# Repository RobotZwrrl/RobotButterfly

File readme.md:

# Robot Butterfly

[Robot Butterfly](http://robotzwrrl.xyz/robot-butterfly/) invites you to experience nature's elegance alongside it, while interacting with the surrounding wilderness! [Available now as a kit](https://robotmissions.org/store/) to build yourself. 

For more information, check out: [robotzwrrl.xyz/robot-butterfly](http://robotzwrrl.xyz/robot-butterfly/). As well, see the [instructions](https://robotzwrrl.xyz/robot-butterfly/instructions/chapter01.php) to build your own!

Robot Butterfly's design files are released as open source hardware, provided under these unique terms: If you replicate it, please take a photo of it in nature and email it to me with the city and its nickname! ☺️

---

## Bug Fix 12-15-24

A 3D printable bugfix is available! The three pieces to print are:

- [Servo Horn Indent L](https://github.com/RobotGrrl/RobotButterfly/blob/main/3dprint/servo_horn_indent_L_v1.0.stl)
- [Servo Horn Indent R](https://github.com/RobotGrrl/RobotButterfly/blob/main/3dprint/servo_horn_indent_R_v1.0.stl)
- [Spacer Back](https://github.com/RobotGrrl/RobotButterfly/blob/main/3dprint/spacer_back_v1.1.stl)

The servo horn piece has been updated to work with the new horns that have an indent, rather than being flat in the previous version. The horn is placed on the side that has the arrow indicator. The fasteners go through holes #1 and #4. See photo below for reference.

The spacer back piece has been updated to have clearance for the chamfer around the switch housing on the enclosure. This provides a cleaner fit and smoother lid installation process.

---

## Electronics

The Butterfly Chonky board connects with [Keystone](https://github.com/RobotGrrl/Keystone) and [Boostlet!](https://github.com/RobotGrrl/boostlet). Those two boards are also open source, and can be found in these repositories:

- https://github.com/RobotGrrl/boostlet
- https://github.com/RobotGrrl/Keystone

### What do the LEDs mean?

There are a few LEDs that are visible through the windows on the back of the enclosure.

On Chonky, there are two yellow 5 mm LEDs. On the left hand side, is D2. In the firmware, D2 is `LED_COMMS_PIN` (pin 5). On the right hand side, this is D1. In the firmware, D1 is `LED_HEARTBEAT_PIN` (pin 13).

LEDs from Keystone are also visible through the LED ports on the back side of the enclosure. As well, sometimes their brightness reflects in Chonky’s 5 mm LEDs. On the left hand side is power. The power LED is on all the time. On the right hand side are TX and RX. The TX and RX LEDs are activated whenever there is data on the serial port. This can be useful for a visual check, but it also just looks techno cool.

In the inaugural version, all the LEDs are yellow, which can sometimes make it tricky to visually differentiate between Chonky and Keystone's LEDs. This will be changed in a future production revision :)

---

## Manufacturing

| Piece                     | Layer height    | Supports                   | Infill | Shells | Notes                                              |
| ------------------------- | --------------- | -------------------------- | ------ | ------ | -------------------------------------------------- |
| enclosure_v1.0.stl        | 0.25 mm DRAFT   | Everwhere, Organic         | 15%    | 2      | \-                                                 |
| neopixel_bracket_v1.0.stl | 0.25 mm DRAFT   | Everwhere, Organic         | 15%    | 3      | Prints standing up                                 |
| battery_bracket_v1.0.stl  | 0.25 mm DRAFT   | Supports to build platform | 15%    | 2      | Hiya!' faces up, Top fill pattern: Octogram Spiral |
| lid_v1.1.stl              | 0.25 mm DRAFT   | None                       | 15%    | 3      | Chamfer side down                                                 |
| servo_bracket_v1.0.stl    | 0.25 mm DRAFT   | None                       | 15%    | 2      | Prints face down                                   |
| servo_horn_indent_L_v1.0.stl     | 0.20 mm QUALITY | None                       | 20%    | 4      | \-                                                 |
| servo_horn_indent_R_v1.0.stl     | 0.20 mm QUALITY | None                       | 20%    | 4      | \-                                                 |
| cover_v1.0.stl            | 0.25 mm DRAFT   | None                       | 15%    | 2      | Cool!' faces up                                    |
| spacer_back_v1.1.stl      | 0.25 mm DRAFT   | None                       | 15%    | 2      | Chamfer side down                                  |
| spacer_front_v1.0.stl     | 0.25 mm DRAFT   | None                       | 15%    | 2      | Chamfer side down                                  |
| wing_L_v1.0.stl           | 0.25 mm DRAFT   | None                       | 15%    | 3      | Top & bottom fill pattern: Archimedian Chords. Print 1st layer at a very slow speed.      |
| wing_R_v1.0.stl           | 0.25 mm DRAFT   | None                       | 15%    | 3      | Top & bottom fill pattern: Archimedian Chords. Print 1st layer at a very slow speed.      |

---

## Firmware

**Firmware is in active development**

Download the [Robot Butterfly library](https://github.com/RobotZwrrl/RobotButterfly/tree/main/firmware/library/RobotButterfly) and install it into your Arduino library folder _(for example: ~/Documents/Arduino/libraries)_.

### Boards Manager

In the Arduino IDE boards manager (Tools > Board > Board Manager), search for **esp32**. Under **esp32 by Espressif Systems**, choose **2.0.4**, and install it.

### Library Dependencies

In the Arduino IDE library manager (Tools > Manage Libraries), please install the following libraries with the designated versions:

- [Streaming](https://github.com/janelia-arduino/Streaming) - v5.0.0
- [movingAvg](https://github.com/JChristensen/movingAvg) - v2.3.2
- [MPU6050](https://github.com/ElectronicCats/mpu6050) - v1.4.3
- [Adafruit Neopixel](https://github.com/adafruit/Adafruit_NeoPixel) - v.1.12.4
- [ESP32Servo](https://github.com/madhephaestus/ESP32Servo) - v3.0.6 
- [ServoEasing](https://github.com/ArminJo/ServoEasing) - v3.4.0
- [DHT](https://github.com/adafruit/DHT-sensor-library) - v1.4.6
- [Adafruit Unified Sensor](https://github.com/adafruit/Adafruit_Sensor) - v1.1.15 
- [HC-SR04](https://github.com/d03n3rfr1tz3/HC-SR04) - v1.1.3 

### Upload Code

Here's how to upload code to Robot Butterfly!

_Please see steps above to ensure all dependencies are installed properly_

1. Tools > Board > esp32 > Set board to **ESP32 Dev Module**

2. Tools > Set upload speed to **115200 baud** (at the bottom of the menu)

3. Tools > Set CPU speed to **80 MHz** (first setting after a divider in the menu)

4. Tools > Manage Libraries
There are library dependencies that will need to be downloaded, see list above

5. Open a Robot Butterfly example sketch

6. Plug in Robot Butterfly

7. Tools > Port > Select the port

8. Upload

9. Congrats! You have uploaded code to Robot Butterfly!

### Animations

For developers - here's how to make your own animation (servo and neopixel):

1. Add identifier to enum servoAnimName

`SERVO_ANIM_SOARING`

2. Add the run function prototype

`void runServoAnim_soaring(struct ServoAnimation *animation);`

3. Write the run function

`void runServoAnim_soaring(struct ServoAnimation *a) { ... }`

4. Write the init function

`void initServoAnim_soaring(struct ServoAnimation *a) { ... }`

5. Add the case to setServoAnim

`case SERVO_ANIM_SOARING: 
initServoAnim_soaring(a); 
break;`

6. Call the animation to run it!

`setServoAnim(&servo_animation_alert, SERVO_ANIM_SOARING, SERVO_ANIM_ALERT); 
startServoAnim(&servo_animation_alert);`

---

## Debugging

Please see [this page for debugging FAQ](https://robotzwrrl.xyz/robot-butterfly/instructions/debugging.php).

---

## License

Robot Butterfly (C) Copyright Erin RobotZwrrl, Robot Missions Inc.

05-30-24 v1.0

[RobotZwrrl.xyz/robot-butterfly](http://RobotZwrrl.xyz/robot-butterfly)

[RobotMissions.org](https://RobotMissions.org)

This hardware is released under:

CERN Open Hardware License Version 2.0 - Permissive (CERN-OHL-P)

[https://cern-ohl.web.cern.ch/](https://cern-ohl.web.cern.ch/)

The software is released under:

The MIT License

[https://opensource.org/license/mit](https://opensource.org/license/mit)

The documentation is released under:

CC-BY-SA-4.0

[https://creativecommons.org/licenses/by-sa/4.0/](https://creativecommons.org/licenses/by-sa/4.0/)

_Disclaimer: Distributed as is. No warranty is given. Not responsible or liable for any damage or harm that result from this product._

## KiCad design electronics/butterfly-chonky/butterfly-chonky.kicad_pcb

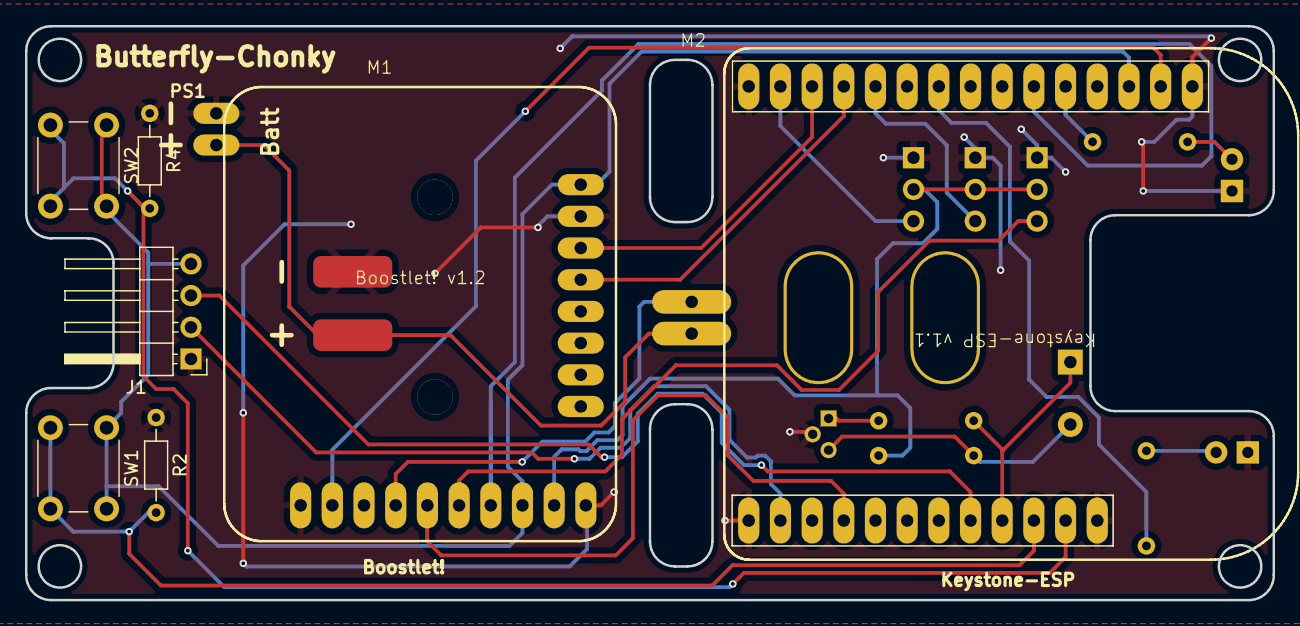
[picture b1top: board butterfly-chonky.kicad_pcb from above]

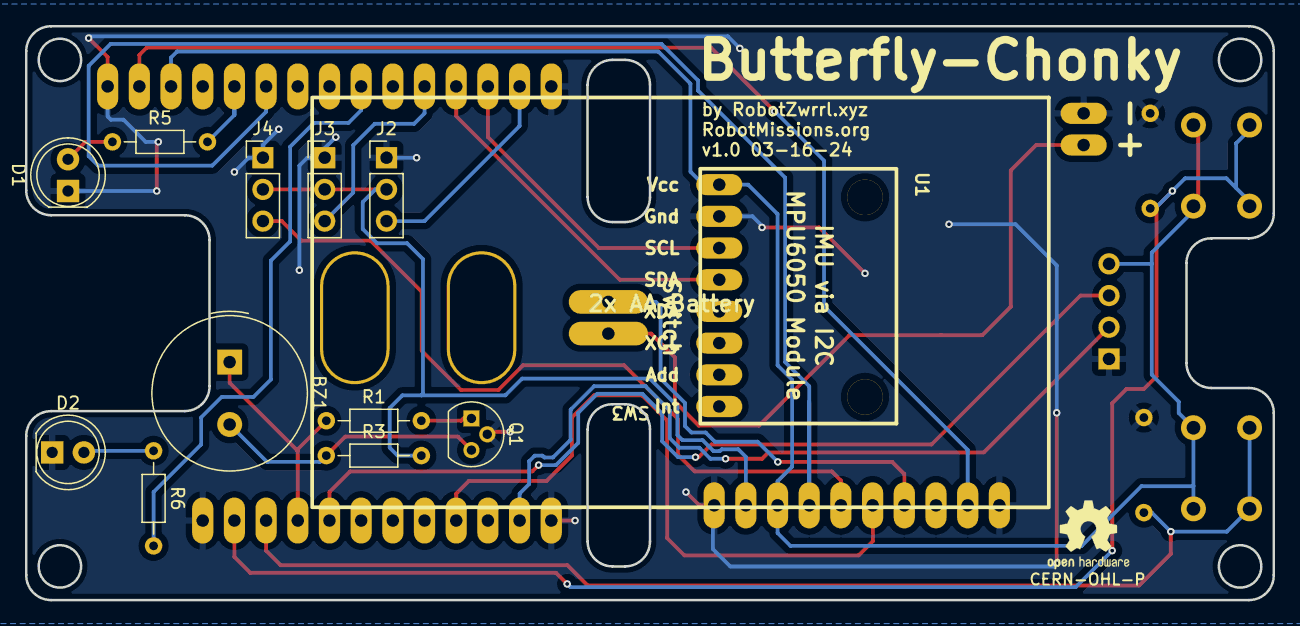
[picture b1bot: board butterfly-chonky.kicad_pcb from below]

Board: 2 copper layers, 100.0 x 46.0 mm, 21 parts (13 on the bottom side), 24 nets.

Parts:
BZ1: Buzzer; Buzzer_TDK_PS1240P02BT_D12.2mm_H6.5mm
D1, D2: LED; LED_D5.0mm_Clear
J1: Conn_01x04_Pin; PinHeader_1x04_P2.54mm_Horizontal
J2, J3, J4: Conn_01x03_Pin; PinHeader_1x03_P2.54mm_Vertical
M1: Boostlet_v1.2
M2: Keystone-ESP_v1.1
PS1: 2xAA_Battery_Module
Q1: 2N2222; TO-92
R1: 2K; R_Axial_DIN0204_L3.6mm_D1.6mm_P7.62mm_Horizontal
R2, R4: 10k; R_Axial_DIN0204_L3.6mm_D1.6mm_P7.62mm_Horizontal
R3, R5, R6: 330; R_Axial_DIN0204_L3.6mm_D1.6mm_P7.62mm_Horizontal
SW1, SW2: SW_Push; SW_PUSH_6mm_H5mm
SW3: Switch_Header
U1: MPU6050_Module

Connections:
5V: J2.2, J3.2, J4.2, M1.9 (5V), R3.2
/BATT_SIG: M1.5 (BATT_SIG), M2.19 (IO34)
/BUTTON_1: M2.25 (IO27), R2.2, SW1.2
/BUTTON_2: M2.26 (IO14), R4.2, SW2.2
/BUZZER: BZ1.1 (+), M2.24 (IO26), R1.1
/LED_COMMS: M2.7 (IO5), R6.2
/LED_HEARTBEAT: M2.11 (IO13), R5.2
/NEO_IN: M1.7 (NEO_IN1), M2.10 (IO4)
/NEO_OUT: J4.3, M1.6 (NEO_OUT1)
/SCL: M2.3 (IO22), U1.3 (SCL)
/SDA: M2.4 (IO21), U1.4 (SDA)
/SERVO_L: J2.3, M2.2 (IO23)
/SERVO_R: J3.3, M2.5 (IO19)
/ULTRASONIC_IN: J1.2, M2.17 (IO36)
/ULTRASONIC_OUT: J1.3, M2.23 (IO25)
/V_BATT: M1.4 (V_BATT), SW3.2
GND: D1.1 (K), D2.1 (K), J1.1, J2.1, J3.1, J4.1, M1.1 (GND), M1.10 (GND), M2.1 (GND), M2.15 (GND), M2.16 (GND), M2.27 (GND), PS1.1 (Gnd), Q1.2 (E), R2.1, R4.1, U1.2 (Gnd)
unnamed: BZ1.2 (-), Q1.3 (C), R3.1
unnamed: D1.2 (A), R5.1
unnamed: D2.2 (A), R6.1
unnamed: M1.2 (V_BUS), M2.14 (VBUS)
unnamed: PS1.2 (V_Batt), SW3.1
unnamed: Q1.1 (B), R1.2
VCC: J1.4, M1.8 (3.3V), M2.13 (VCC), SW1.1, SW2.1, U1.1 (Vcc)

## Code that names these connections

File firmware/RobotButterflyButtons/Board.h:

#define SERVO_LEFT_HOME     900
#define SERVO_LEFT_UP       1900
#define SERVO_LEFT_DOWN     500

#define SERVO_RIGHT_HOME    1400
#define SERVO_RIGHT_UP      500
#define SERVO_RIGHT_DOWN    1900

#define SERVO_LEFT_PIN      19
#define SERVO_RIGHT_PIN     23

#define NEOPIXEL_PIN        4
#define NEOPIXEL_COUNT      8
#define LED_HEARTBEAT_PIN   13
#define LED_COMMS_PIN       5
#define BUZZER_PIN          26

#define MIC_PIN             39
#define BATT_SIG_PIN        34
#define LDR_PIN             35

#define BUTTON1_PIN         14   // left
#define BUTTON2_PIN         27   // right
#define BUTTON3_PIN         15

#define ULTRASONIC_IN_PIN   36   // echo
#define ULTRASONIC_OUT_PIN  25   // trig
#define PROX_L_PIN          32   // cut solder bridge on chonky
#define EXTRA_PIN           32
#define PROX_R_PIN          33   // cut solder bridge on chonky
#define DHT11_PIN           33

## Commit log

2024-02-11 Wizard to guide calibration of servos
2024-02-11 Continuous movement test for servo longevity
2024-03-16 Chonky dev bordzorz1
2024-04-22 Zweeeop, ZweeeeeeOP, zwoop zwuup
2024-05-14 Yip Yip Yawooooooo
2024-05-30 3d files released to the world
2024-05-30 Important detail
2024-05-30 hiya
2024-05-31 Manufacturing deeeeeetail
2024-06-15 Temperature and Humidity
2024-06-16 Oups
2024-06-28 orange blips
2024-06-28 purple blips
2024-06-29 pesky little sensor
2024-06-29 s i m p l i f y
2024-06-30 Added chamfer to underside of lid for nicer printing
2024-06-30 More reliable stop and restart of Task before watchdog
2024-06-30 Lid 1.1 info
2024-06-30 Timer stuffs
2024-06-30 Ultrasonic multi task
2024-07-02 blep blep blep blep not working reliably blep
2024-07-05 Sigh
2024-07-05 forgot to upload this
2024-07-05 update 3d files
2024-07-06 might not be the best method
2024-07-10 Scratch this
2024-07-10 WOOT! It's working
2024-07-20 Gonna re-do this with mutexes probably
2024-07-24 Semaphore callbacks
2024-08-05 Mutex trying it
2024-08-05 Event driven mutex
2024-08-05 New new new animations and tidy ups
2024-08-19 dee dee dee debouncing
2024-08-25 B b b b B utton update
2024-08-25 BbbbButtons
2024-09-03 Hang a robot from a tree with this piece! Cool
2024-09-03 So curious as to why this does not work
2024-09-03 Curiouser and curiouser
2024-09-06 This works meow
2024-12-15 Servo horn bug fix
2024-12-15 Lanyard attachment increase base height by a few tenths of mm to prevent fasteners from making contact with surface
2024-12-15 Assembly update with bug fix for spacer back
2024-12-15 Spacer Back bug fix
2024-12-15 Readme update
2024-12-15 Bugfix photos for documentation
2024-12-15 .DS_Store banished!
2024-12-15 Bugfix documentation
2024-12-18 Tricky buttons
2024-12-20 Another go at buttons
2024-12-20 Double click button try
2024-12-20 Better buttons
2024-12-20 Buttons complete
2024-12-21 Buttons in FreeRTOS task
2024-12-21 Rememberingberingbering semaphore
2025-01-12 Instructions renderer
2025-01-19 Nudge html this way and that way
2025-01-20 Linky to the instructions! zeewoooot
2025-02-20 Update task template
2025-02-20 Testing ignore
2025-02-20 The reason why gitignore did not work was because git pull was not done locally before adding the files. Sigh Lol
2025-02-20 Let's test this again
2025-02-20 Settings in progress
2025-02-20 Add info about the LEDs from the instructions
2025-02-20 meep
2025-02-20 Wifi even when turning it off and on and off and on again
2025-02-22 Organise
2025-02-22 Wifi task and improvements
2025-02-24 IMU basic
2025-02-25 IMU work in progress
2025-02-25 IMU WIP
2025-02-27 IMU refactoring and organising
2025-02-27 IMU orientation detection
2025-02-27 IMU event detection
2025-03-03 Print IMU stats and some fine tuning
2025-03-03 IMU callbacks added
2025-03-03 Tidy up
2025-03-03 IMU RTOS Task
2025-03-11 Pretty colours
2025-03-17 Organised LED colours
2025-03-17 Neo animations work in progress
2025-03-17 Tidy up, refactor, fix an off-by-one error
2025-03-17 Start neo anim api
2025-03-17 Squiggle animation bug fixes
2025-03-17 set speed
2025-03-18 More tidy up Neo Animations
2025-03-18 Tidy up Neo Animations
2025-03-18 pretty cool
2025-03-18 Matchy and tidy
2025-03-20 imu api and tidy up
2025-03-20 Sway animation
2025-03-20 new servo animations
2025-03-21 flutter servo animation
2025-03-21 final animations
2025-03-21 Jingles musical buzzer sounds yay
2025-03-22 redo colour values for brightness = 20
2025-03-22 sensors work in progress
2025-03-23 sensor struct, atomic wip
2025-03-24 timer fixes and sensor progress
2025-03-24 sensor update function improvements
2025-03-24 sensor cleanup and ambient improvements
2025-03-24 temperature sensor work in progress
2025-03-25 fix up the interrupt and add in additional sensors for long test
2025-03-26 prior to switching dht11 libraries
2025-03-27 this dht11 lib works
2025-03-27 Sensor improvements
2025-03-27 DHT11 sensor read toggle
2025-03-27 move previous revision to archive
2025-03-27 Happy five sensors
2025-03-27 meep meep
2025-03-28 meep meep 2
2025-03-28 archive old ultrasonic version
2025-03-28 new ultrasonic version
2025-03-28 proximity updates
2025-03-28 proximity moving average filter
2025-03-28 archive old servo movements
2025-03-31 Neo range animation
2025-03-31 Documentation about adding custom animation
2025-03-31 formatting
2025-04-02 some more neo animations and looped callback
2025-04-02 Sprinkle animation
2025-04-02 Rainbows\!
2025-04-03 breathe animation
2025-04-03 cycle 8 animation
2025-04-03 cycle 3 neo animation
2025-04-03 ambiance neo animations
2025-04-05 sound api
2025-04-05 neo anim api cleaner
2025-04-05 Neo animation uno
2025-04-05 archive old program
2025-04-07 servo anim api cleaning
2025-04-07 wip state machine improvements
2025-04-08 state machine good
2025-04-08 archive old sketches
2025-04-08 imu timer update
2025-04-08 Sound buzzer control update
2025-04-08 Button modifications
2025-04-08 State machine improvements
2025-04-09 Example messy integration
2025-04-09 integrated 1 updates
2025-04-21 bettery battery
2025-04-21 archive integrated v1
2025-04-21 bettery battery integrated
2025-04-21 Duo for Uno animation
2025-04-21 calibration mode
2025-04-27 final frozen version
2025-04-30 function pointers for buttons
2025-04-30 imu function pointers
2025-04-30 Neo animation function pointers
2025-04-30 proximity function pointer
2025-04-30 function pointer into a struct
2025-04-30 sensor function pointers
2025-04-30 servo animation function pointers
2025-04-30 sound function pointer
2025-04-30 null check
2025-05-01 narrowly avoided disaster
2025-05-02 progress on library
2025-05-03 neo animation module
2025-05-03 mini tidy up servo anims
2025-05-03 servo animation module
2025-05-03 woops
2025-05-03 minor sensor tweaks
2025-05-03 library sensor module
2025-05-03 library proximity module
2025-05-03 minor proximity tidying
2025-05-03 minor sound change
2025-05-03 something in state machine
2025-05-03 library - added state machine
2025-05-04 work in progress callbacks
2025-05-04 client callbacks added, example sketch done
2025-05-04 buttons rtos sandbox sketch
2025-05-05 stack sizes
2025-05-05 added freertos tasks to modules
2025-05-05 rtos enabled
2025-05-05 example code
2025-05-07 integrated example sketch
2025-05-07 making sure this is up to date
2025-05-07 v1.0.0
2025-05-07 documentation update
2025-05-07 documentation beep boop
2025-05-08 first version of the library frozen
2025-05-08 library v1.0.1
2025-05-08 v1.0.2 hehe
2025-05-11 aa batt bugfix
2025-05-17 state machine timer bug fix
2025-06-04 Organised schematic
2025-07-03 Added documentation and firmware license
2025-07-03 Formatting fix
2025-08-15 festival firmware
2025-08-16 latest festival code
2025-08-23 Projector interactive experience code
2025-08-23 little timing tweak
2025-08-23 Interactive vis program
2025-08-24 Improvements
2025-08-24 final tweak before the performance
2025-08-24 minor tweak to have leds on
2025-08-24 minor tweak to the vis dynamics
2025-09-27 Code for the season finale of robot in the park
2026-01-14 work in progress - neopixel mqtt
